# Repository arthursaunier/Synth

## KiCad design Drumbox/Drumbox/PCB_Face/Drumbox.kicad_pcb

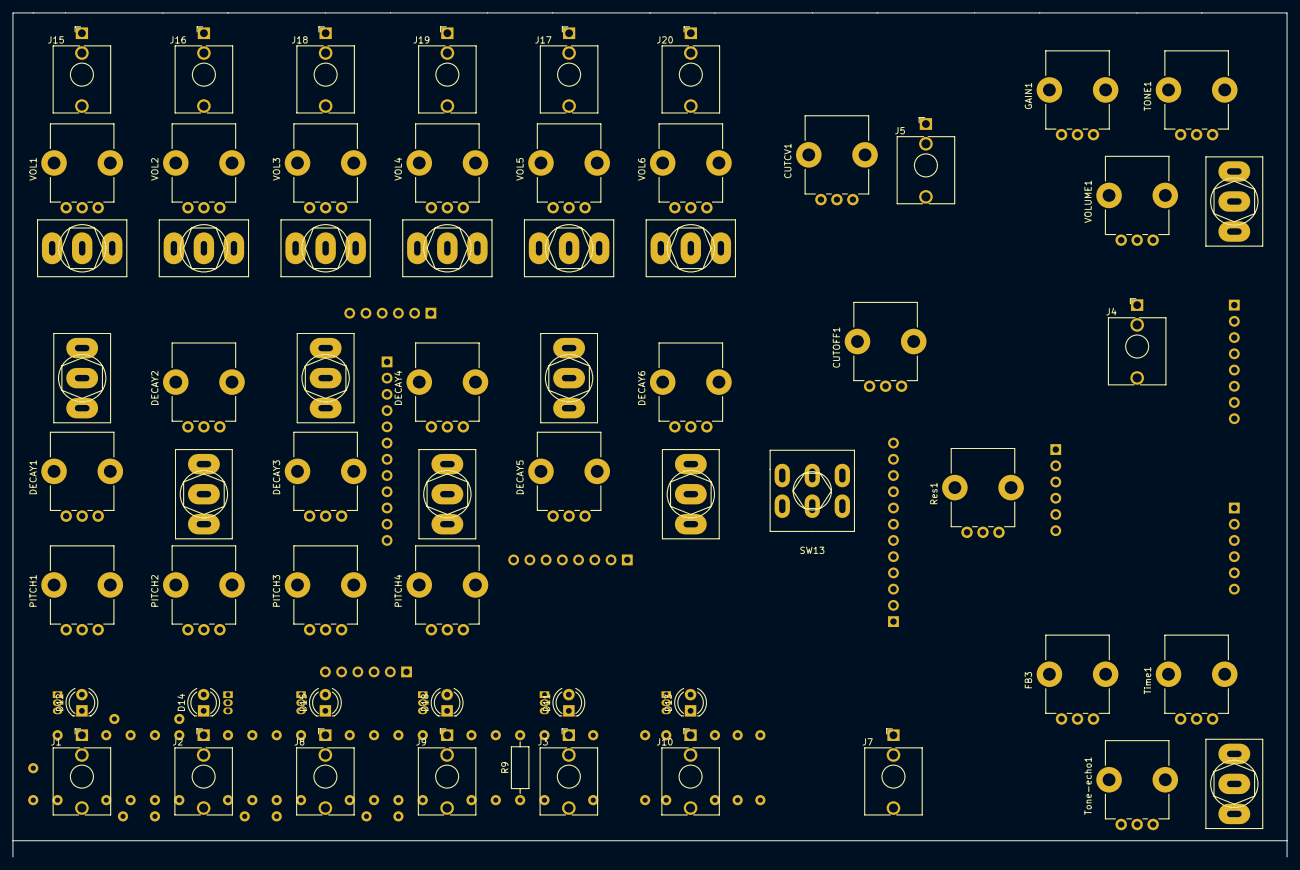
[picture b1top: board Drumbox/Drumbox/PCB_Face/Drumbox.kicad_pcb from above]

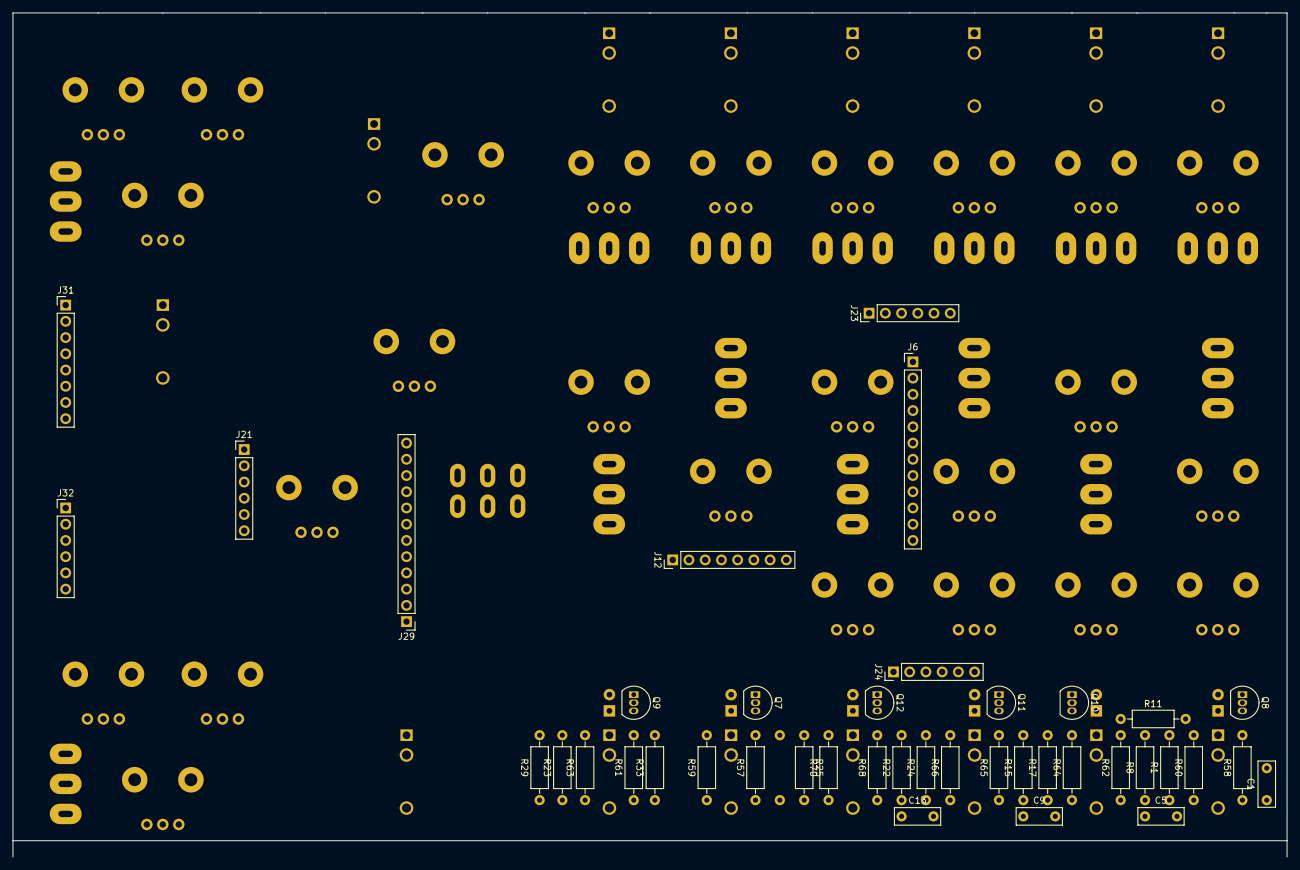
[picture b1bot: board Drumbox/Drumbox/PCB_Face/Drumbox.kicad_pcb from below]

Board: 2 copper layers, 199.4 x 132.1 mm, 103 parts (41 on the bottom side), 86 nets, no tracks yet.

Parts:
C1: 150nF; C_Disc_D7.0mm_W2.5mm_P5.00mm
C5: 33nF; C_Disc_D7.0mm_W2.5mm_P5.00mm
C9: 39nF; C_Disc_D7.0mm_W2.5mm_P5.00mm
C13: 4.7nF; C_Disc_D7.0mm_W2.5mm_P5.00mm
CUTCV1: 100k; Potentiometer_Bourns_PTV09A-1_Single_Vertical
CUTOFF1: 100k; Potentiometer_Bourns_PTV09A-1_Single_Vertical
D11: LED5; LED_D4.0mm
D12: LED1; LED_D4.0mm
D13: LED6; LED_D4.0mm
D14: LED2; LED_D4.0mm
D15: LED3; LED_D4.0mm
D18: LED4; LED_D4.0mm
DECAY1, DECAY2, DECAY3, DECAY4: 470k; Potentiometer_Bourns_PTV09A-1_Single_Vertical
DECAY5, DECAY6: 100k; Potentiometer_Bourns_PTV09A-1_Single_Vertical
FB3: 100k; Potentiometer_Bourns_PTV09A-1_Single_Vertical
GAIN1: 100k; Potentiometer_Bourns_PTV09A-1_Single_Vertical
J1: Bass IN; Jack_3.5mm_QingPu_WQP-PJ398SM_Vertical_CircularHoles
J2: HBonga IN; Jack_3.5mm_QingPu_WQP-PJ398SM_Vertical_CircularHoles
J3: Snare IN; Jack_3.5mm_QingPu_WQP-PJ398SM_Vertical_CircularHoles
J4: Aux-IN; Jack_3.5mm_QingPu_WQP-PJ398SM_Vertical_CircularHoles
J5: FilterCV; Jack_3.5mm_QingPu_WQP-PJ398SM_Vertical_CircularHoles
J6, J29: Conn_01x12_Male; PinHeader_1x12_P2.54mm_Vertical
J7: Mono-Out; Jack_3.5mm_QingPu_WQP-PJ398SM_Vertical_CircularHoles
J8: LBonga IN; Jack_3.5mm_QingPu_WQP-PJ398SM_Vertical_CircularHoles
J9: Clave IN; Jack_3.5mm_QingPu_WQP-PJ398SM_Vertical_CircularHoles
J10: HiHat IN; Jack_3.5mm_QingPu_WQP-PJ398SM_Vertical_CircularHoles
J12, J31: Conn_01x08_Male; PinHeader_1x08_P2.54mm_Vertical
J15: Bass OUT; Jack_3.5mm_QingPu_WQP-PJ398SM_Vertical_CircularHoles
J16: HBonga OUT; Jack_3.5mm_QingPu_WQP-PJ398SM_Vertical_CircularHoles
J17: Snare OUT; Jack_3.5mm_QingPu_WQP-PJ398SM_Vertical_CircularHoles
J18: LBonga OUT; Jack_3.5mm_QingPu_WQP-PJ398SM_Vertical_CircularHoles
J19: Clave OUT; Jack_3.5mm_QingPu_WQP-PJ398SM_Vertical_CircularHoles
J20: HiHat OUT; Jack_3.5mm_QingPu_WQP-PJ398SM_Vertical_CircularHoles
J21, J23, J24, J32: Conn_01x06_Male; PinHeader_1x06_P2.54mm_Vertical
PITCH1, PITCH2, PITCH3, PITCH4: 10k; Potentiometer_Bourns_PTV09A-1_Single_Vertical
Q7, Q8, Q9, Q10, Q11, Q12: 2N3904; TO-92_Inline
R1, R8, R15, R22: 12k; R_Axial_DIN0207_L6.3mm_D2.5mm_P10.16mm_Horizontal
R9, R23, R33: 4k7; R_Axial_DIN0207_L6.3mm_D2.5mm_P10.16mm_Horizontal
R11, R25, R57, R58, R61, R62, R65, R68: 47k; R_Axial_DIN0207_L6.3mm_D2.5mm_P10.16mm_Horizontal
R17, R24: 27k; R_Axial_DIN0207_L6.3mm_D2.5mm_P10.16mm_Horizontal
R29: 1M; R_Axial_DIN0207_L6.3mm_D2.5mm_P10.16mm_Horizontal
R59, R60, R63, R64, R66, R70: 2.2k; R_Axial_DIN0207_L6.3mm_D2.5mm_P10.16mm_Horizontal
Res1: 100k; Potentiometer_Bourns_PTV09A-1_Single_Vertical
SW1: Mute-1; SW_Toggle_Blue_wSlots
SW2: Mute-2; SW_Toggle_Blue_wSlots
SW3: Mute-3; SW_Toggle_Blue_wSlots
SW4: Mute-4; SW_Toggle_Blue_wSlots
SW5: Mute-5; SW_Toggle_Blue_wSlots
SW6: Mute-6; SW_Toggle_Blue_wSlots
SW7: Fx1; SW_Toggle_Blue_wSlots
SW8: Fx3; SW_Toggle_Blue_wSlots
SW9: Fx5; SW_Toggle_Blue_wSlots
SW10: Fx2; SW_Toggle_Blue_wSlots
SW11: Fx4; SW_Toggle_Blue_wSlots
SW12: Fx6; SW_Toggle_Blue_wSlots
SW13: Hpass/Lpass Switch; SW_DPDT_Toggle
SW14: Stupid ON/OFF; SW_Toggle_Blue_wSlots
SW15: Echo ON/OFF; SW_Toggle_Blue_wSlots
TONE1: 10k; Potentiometer_Bourns_PTV09A-1_Single_Vertical
Time1: 100k; Potentiometer_Bourns_PTV09A-1_Single_Vertical
Tone-echo1: 100k; Potentiometer_Bourns_PTV09A-1_Single_Vertical
VOL1, VOL2, VOL3, VOL4, VOL5, VOL6: 10k; Potentiometer_Bourns_PTV09A-1_Single_Vertical
VOLUME1: 50k; Potentiometer_Bourns_PTV09A-1_Single_Vertical

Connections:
+12V: J21.2, J29.2, R23.1, R29.1, R59.1, R60.1, R63.1, R64.1, R66.1, R70.1
AuxIn: J4.T, J21.3
CutCV: CUTCV1.2, J29.11
Cutoff: CUTOFF1.2, J29.10
DEIn1: DECAY1.1, J6.6
DEIn2: DECAY2.1, J6.5
DEIn3: DECAY3.1, J6.4
DEIn4: DECAY4.1, J6.3
DEIn5: CUTCV1.1, D11.1, D12.1, D13.1, D14.1, D15.1, D18.1, DECAY5.2, DECAY5.3, DECAY6.2, DECAY6.3, J1.S, J2.S, J3.S, J4.S, J5.S, J6.1, J6.2, J7.S, J8.S, J9.S, J10.S, J12.1, J12.2, J12.3, J15.S, J16.S, J17.S, J18.S, J19.S, J20.S, J21.1, J21.6, J29.1, J29.3, J29.4, J29.12, J32.1, PITCH2.1, PITCH3.1, PITCH4.1, R1.2, R8.2, R9.2, R11.1, R15.2, R22.2, R25.1, R33.2, Res1.1, SW13.6, Time1.3, Tone-echo1.3, VOL1.3, VOL2.3, VOL3.3, VOL4.3, VOL5.3, VOL6.3, VOLUME1.3
DEOut1: DECAY1.2, DECAY1.3, J6.12
DEOut2: DECAY2.2, DECAY2.3, J6.11
DEOut3: DECAY3.2, DECAY3.3, J6.10
DEOut4: DECAY4.2, DECAY4.3, J6.9
DEOut5: DECAY5.1, J6.8
DEOut6: DECAY6.1, J6.7
FBIn: FB3.1, J32.3
FBOut: FB3.2, J32.2
Filter: J31.6, SW7.1, SW8.1, SW9.1, SW10.1, SW11.1, SW12.1, SW13.3, SW13.4, SW15.1
FilterCV: CUTCV1.3, J5.T, J21.4
FilterOut: J7.T, J21.5
Fx: SW7.3, SW8.3, SW9.3, SW10.3, SW11.3, SW12.3, SW14.2
Fx1: SW1.1, SW7.2
Fx2: SW2.1, SW10.2
Fx3: SW3.1, SW8.2
Fx4: SW4.1, SW11.2
Fx5: SW5.1, SW9.2
Fx6: SW6.1, SW12.2
FxEcho: J31.5, SW14.1, SW15.2, VOLUME1.2
FxEchoIn: J31.7, SW15.3
FxStupidIn: J31.8, SW14.3
GainIn: GAIN1.1, J31.1
GainOut: GAIN1.2, GAIN1.3
Hpass: J29.6, SW13.5
In1: C1.1, J1.T, J24.6, R1.1, R58.1
In2: C5.1, J2.T, J24.5, R8.1, R62.1
In3: C9.1, J8.T, J24.4, R15.1, R65.1
In4: C13.1, J9.T, J24.3, R22.1, R68.1
In5: J3.T, J24.2, R9.1, R57.1
In6: J10.T, J24.1, R33.1, R61.1
LPass: J29.7, SW13.2
Mute1: J15.T, SW1.2, VOL1.2
Mute2: J16.T, SW2.2, VOL2.2
Mute3: J18.T, SW3.2, VOL3.2
Mute4: J19.T, SW4.2, VOL4.2
Mute5: J17.T, SW5.2, VOL5.2
Mute6: J20.T, SW6.2, VOL6.2
unnamed: C5.2, R11.2
unnamed: C9.2, R17.1
unnamed: C13.2, R24.1, R25.2
unnamed: D11.2, Q7.1
unnamed: D12.2, Q8.1
unnamed: D13.2, Q9.1
unnamed: D14.2, Q10.1
unnamed: D15.2, Q11.1
unnamed: D18.2, Q12.1
unnamed: Q7.2, R57.2
unnamed: Q7.3, R59.2
unnamed: Q8.2, R58.2
unnamed: Q8.3, R60.2
unnamed: Q9.2, R61.2
unnamed: Q9.3, R63.2
unnamed: Q10.2, R62.2
unnamed: Q10.3, R64.2
unnamed: Q11.2, R65.2
unnamed: Q11.3, R66.2
unnamed: Q12.2, R68.2
unnamed: Q12.3, R70.2
PIIn1: J12.4, PITCH1.1
PIOut1: J12.8, PITCH1.2, PITCH1.3
PIOut2: J12.7, PITCH2.2, PITCH2.3
PIOut3: J12.6, PITCH3.2, PITCH3.3
PIOut4: J12.5, PITCH4.2, PITCH4.3
ResIn: J29.9, Res1.3
ResOut: J29.8, Res1.2
TimeOut: J32.6, Time1.1, Time1.2
ToneEchoIn: J32.5, Tone-echo1.1
ToneEchoOut: J32.4, Tone-echo1.2
ToneIN: J31.4, TONE1.1, TONE1.2
ToneOUT: J31.3, TONE1.3
Vol1: J23.6, VOL1.1
Vol2: J23.5, VOL2.1
Vol3: J23.4, VOL3.1
Vol4: J23.3, VOL4.1
Vol5: J23.2, VOL5.1
Vol6: J23.1, VOL6.1
VolOut: J31.2, VOLUME1.1

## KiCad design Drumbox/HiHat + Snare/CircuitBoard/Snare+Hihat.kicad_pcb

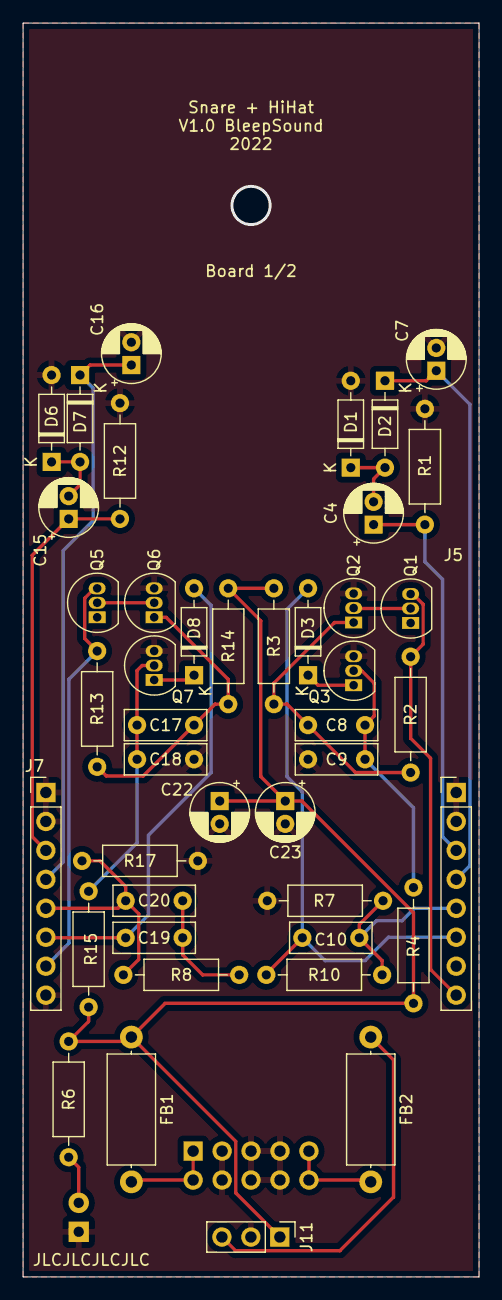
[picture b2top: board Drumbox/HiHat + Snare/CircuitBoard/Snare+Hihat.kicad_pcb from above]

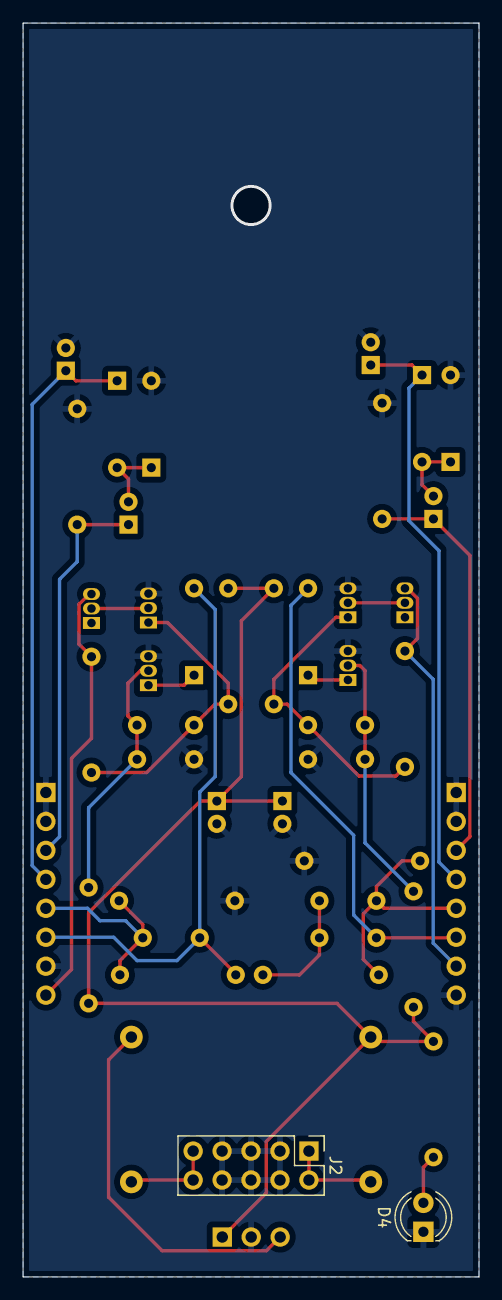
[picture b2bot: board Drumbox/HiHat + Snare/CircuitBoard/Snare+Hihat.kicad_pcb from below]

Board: 2 copper layers, 40.0 x 110.0 mm, 45 parts (2 on the bottom side), 27 nets.

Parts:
C4, C7, C15, C16: 10µF; CP_Radial_D5.0mm_P2.00mm
C8, C17: 1µF; C_Disc_D7.0mm_W2.5mm_P5.00mm
C9: 0.1µF; C_Disc_D7.0mm_W2.5mm_P5.00mm
C10, C20: .1µF; C_Disc_D7.0mm_W2.5mm_P5.00mm
C18: 10nF; C_Disc_D7.0mm_W2.5mm_P5.00mm
C19: 680pF; C_Disc_D7.0mm_W2.5mm_P5.00mm
C22, C23: 100µ; CP_Radial_D5.0mm_P2.00mm
D1, D2, D3, D6, D7, D8: 1N4148; D_DO-35_SOD27_P7.62mm_Horizontal
D4: LED-12V; LED_D4.0mm
FB1, FB2: 10R; L_Axial_L9.5mm_D4.0mm_P12.70mm_Horizontal_Fastron_SMCC
J2: Power Input; PinHeader_2x05_P2.54mm_Vertical
J5, J7: Conn_01x08_Male; PinHeader_1x08_P2.54mm_Vertical
J11: Conn_01x03_Male; PinHeader_1x03_P2.54mm_Vertical
Q1, Q2, Q3, Q5, Q6, Q7: BC546; TO-92_Inline
R1, R3, R12, R14: 4k7; R_Axial_DIN0207_L6.3mm_D2.5mm_P10.16mm_Horizontal
R2, R13: 47k; R_Axial_DIN0207_L6.3mm_D2.5mm_P10.16mm_Horizontal
R4, R7, R15, R17: 1M; R_Axial_DIN0207_L6.3mm_D2.5mm_P10.16mm_Horizontal
R6: 2.2k; R_Axial_DIN0207_L6.3mm_D2.5mm_P10.16mm_Horizontal
R8, R10: 0R; R_Axial_DIN0207_L6.3mm_D2.5mm_P10.16mm_Horizontal

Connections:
+12V: C22.1, C23.1, FB1.1, J11.1, R3.1, R4.1, R6.1, R14.1, R15.1
-12V: FB2.1, J11.3
/DeH: J5.8, Q1.3 (E), R2.1
/HiDH: J7.7, Q5.3 (E), R13.1
/HiH: C16.1, D7.1 (K), J7.4
/HiI: C15.1, J7.3, R12.1
/HiO: C20.2, J7.5, R8.1, R17.1
/Ho: C19.1, D8.2 (A), J7.6
/SnH: C7.1, D2.1 (K), J5.4
/SnI: C4.1, J5.3, R1.1
/SnO: C10.2, J5.5, R7.1, R10.1
/So: C10.1, D3.2 (A), J5.6, R10.2
GND: C7.2, C9.1, C16.2, C18.1, C22.2, C23.2, D1.2 (A), D4.1 (K), D6.2 (A), J2.3, J2.4, J2.5, J2.6, J2.7, J2.8, J5.1, J5.2, J5.7, J7.1, J7.2, J7.8, J11.2, Q2.3 (E), Q3.3 (E), Q6.3 (E), Q7.3 (E), R1.2, R7.2, R12.2, R17.2
unnamed: C4.2, D1.1 (K), D2.2 (A)
unnamed: C8.1, Q2.1 (C), R2.2, R3.2
unnamed: C8.2, C9.2, Q3.2 (B), R4.2
unnamed: C15.2, D6.1 (K), D7.2 (A)
unnamed: C17.1, Q6.1 (C), R13.2, R14.2
unnamed: C17.2, C18.2, Q7.2 (B), R15.2
unnamed: C19.2, C20.1, R8.2
unnamed: D3.1 (K), Q3.1 (C)
unnamed: D4.2 (A), R6.2
unnamed: D8.1 (K), Q7.1 (C)
unnamed: FB1.2, J2.1, J2.2
unnamed: FB2.2, J2.9, J2.10
unnamed: Q1.2 (B), Q2.2 (B)
unnamed: Q5.2 (B), Q6.2 (B)

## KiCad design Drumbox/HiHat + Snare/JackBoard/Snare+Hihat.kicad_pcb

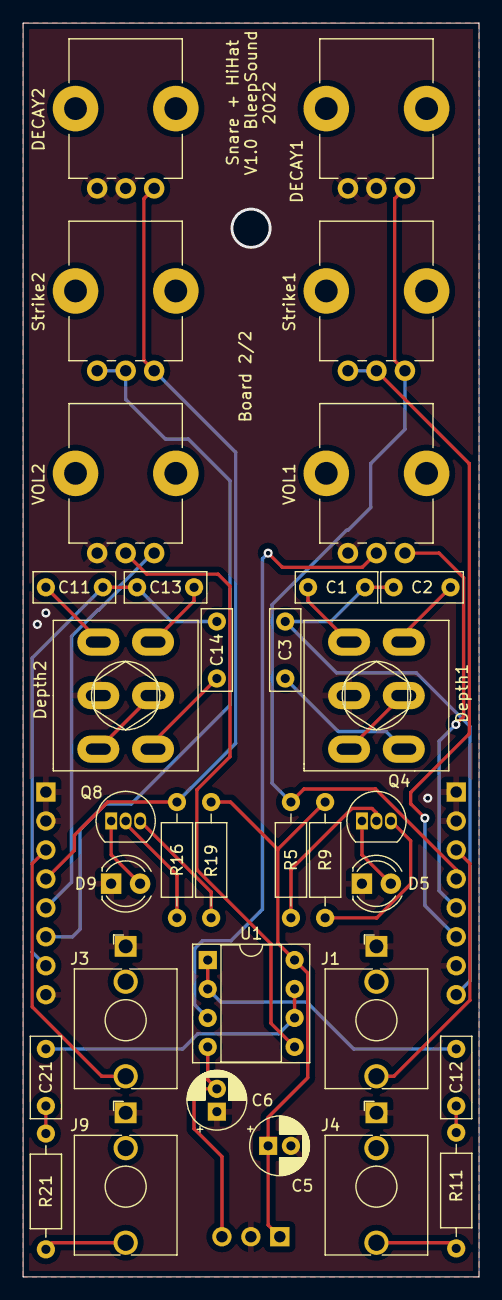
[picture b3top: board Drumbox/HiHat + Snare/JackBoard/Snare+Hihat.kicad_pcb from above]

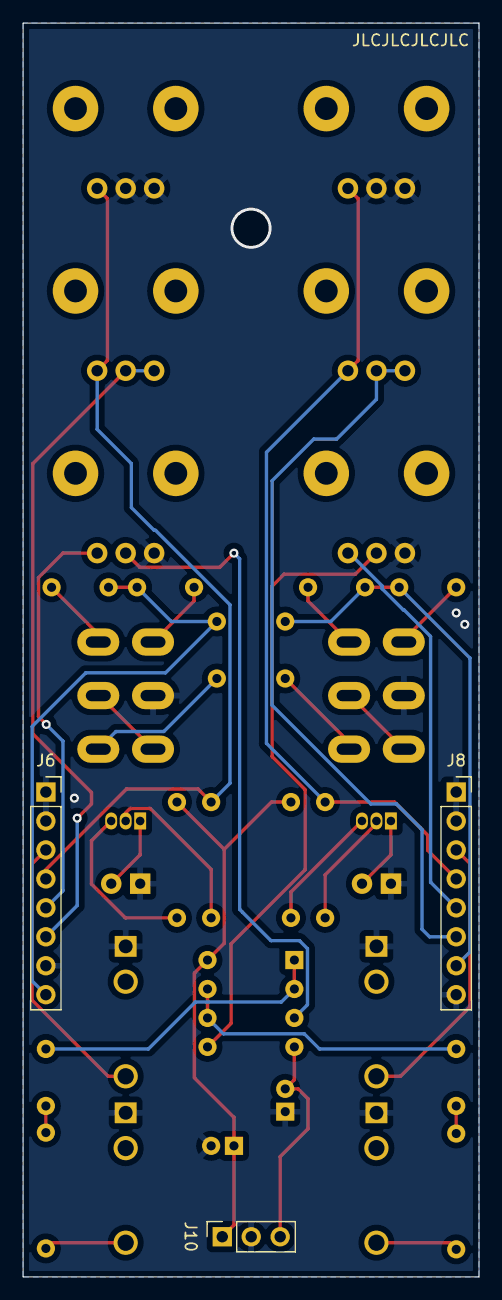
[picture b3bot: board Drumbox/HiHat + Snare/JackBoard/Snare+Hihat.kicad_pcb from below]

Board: 2 copper layers, 40.0 x 110.0 mm, 36 parts (3 on the bottom side), 35 nets.

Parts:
C1, C11, C12, C21: 10µF; C_Disc_D7.0mm_W2.5mm_P5.00mm
C2, C13: 1µF; C_Disc_D7.0mm_W2.5mm_P5.00mm
C3, C14: 0.1µF; C_Disc_D7.0mm_W2.5mm_P5.00mm
C5, C6: 10µ; CP_Radial_D5.0mm_P2.00mm
D5: Trig Snare; LED_D4.0mm
D9: Trig_HiHat; LED_D4.0mm
DECAY1, DECAY2: 100k; Potentiometer_Bourns_PTV09A-1_Single_Vertical
Depth1, Depth2: SW_Push_DPDT; SW_DPDT_Toggle
J1: Snare IN; Jack_3.5mm_QingPu_WQP-PJ398SM_Vertical_CircularHoles
J3: HiHat IN; Jack_3.5mm_QingPu_WQP-PJ398SM_Vertical_CircularHoles
J4: Snare OUT; Jack_3.5mm_QingPu_WQP-PJ398SM_Vertical_CircularHoles
J6, J8: Conn_01x08_Female; PinSocket_1x08_P2.54mm_Vertical
J9: HiHat OUT; Jack_3.5mm_QingPu_WQP-PJ398SM_Vertical_CircularHoles
J10: Conn_01x03_Female; PinSocket_1x03_P2.54mm_Vertical
Q4, Q8: 2N3904; TO-92_Inline
R5, R16: 100k; R_Axial_DIN0207_L6.3mm_D2.5mm_P10.16mm_Horizontal
R9, R11, R19, R21: 1k; R_Axial_DIN0207_L6.3mm_D2.5mm_P10.16mm_Horizontal
Strike1, Strike2: 100k; Potentiometer_Bourns_PTV09A-1_Single_Vertical
U1: TL072; DIP-8_W7.62mm_Socket
VOL1, VOL2: 10k; Potentiometer_Bourns_PTV09A-1_Single_Vertical

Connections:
+12V: C5.1, J10.1, R9.1, R19.1, U1.8 (V+)
-12V: C6.2, J10.3, U1.4 (V-)
/DeH: C1.1, C2.1, C3.1, J6.8
/HiDH: C11.1, C13.1, C14.1, J8.7
/HiH: DECAY2.1, J8.4, R16.1, Strike2.1
/HiI: J3.T, J8.3
/HiO: J8.5, VOL2.1
/Ho: J8.6, Strike2.2, Strike2.3
/SnH: DECAY1.1, J6.4, R5.1, Strike1.1
/SnI: J1.T, J6.3
/SnO: J6.5, VOL1.1
/So: J6.6, Strike1.2, Strike1.3
GND: C5.2, C6.1, D5.1 (K), D9.1 (K), DECAY1.2, DECAY1.3, DECAY2.2, DECAY2.3, Depth1.2 (B), Depth2.2 (B), J1.S, J3.S, J4.S, J6.1, J6.2, J6.7, J8.1, J8.2, J8.8, J9.S, J10.2, VOL1.3, VOL2.3
unnamed: C1.2, Depth1.1 (A)
unnamed: C2.2, Depth1.4 (A)
unnamed: C3.2, Depth1.6 (C)
unnamed: C11.2, Depth2.1 (A)
unnamed: C12.2, R11.2
unnamed: C13.2, Depth2.4 (A)
unnamed: C14.2, Depth2.6 (C)
unnamed: C21.1, U1.6 (-), U1.7
unnamed: C21.2, R21.2
unnamed: D5.2 (A), Q4.1 (E)
unnamed: D9.2 (A), Q8.1 (E)
unnamed: Depth1.3 (C), Depth1.5 (B)
unnamed: Depth2.3 (C), Depth2.5 (B)
unnamed: Q4.2 (B), R5.2
unnamed: Q4.3 (C), R9.2
unnamed: Q8.2 (B), R16.2
unnamed: Q8.3 (C), R19.2
unnamed: J4.T, R11.1
unnamed: J9.T, R21.1
unnamed: C12.1, U1.1, U1.2 (-)
unnamed: U1.3 (+), VOL1.2
unnamed: U1.5 (+), VOL2.2

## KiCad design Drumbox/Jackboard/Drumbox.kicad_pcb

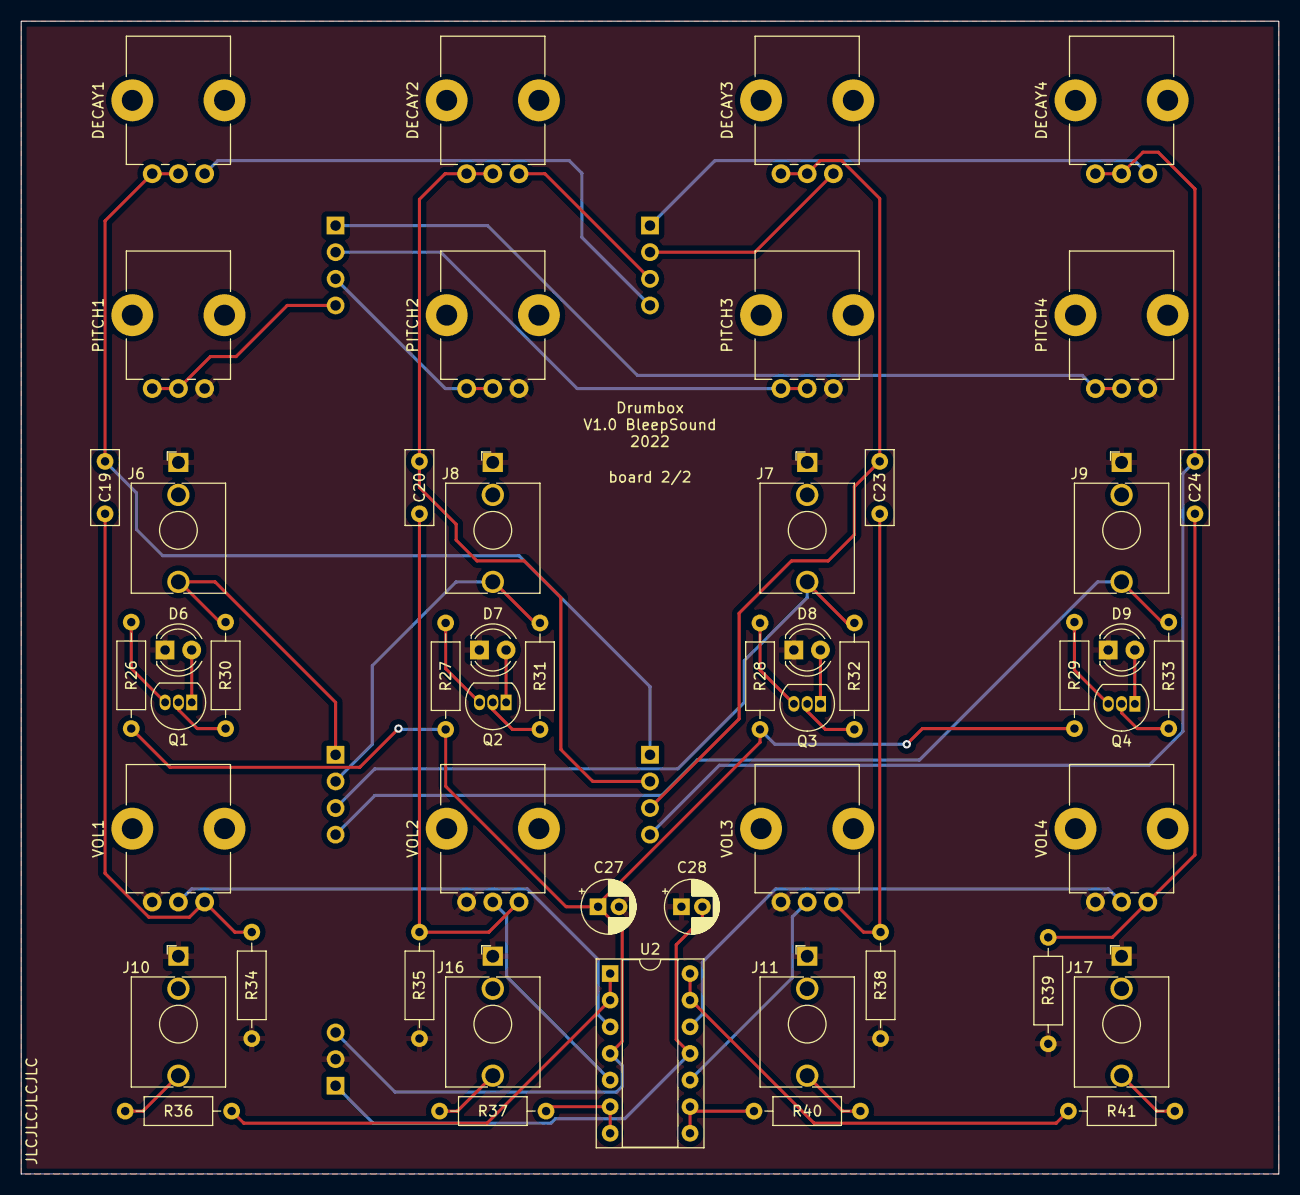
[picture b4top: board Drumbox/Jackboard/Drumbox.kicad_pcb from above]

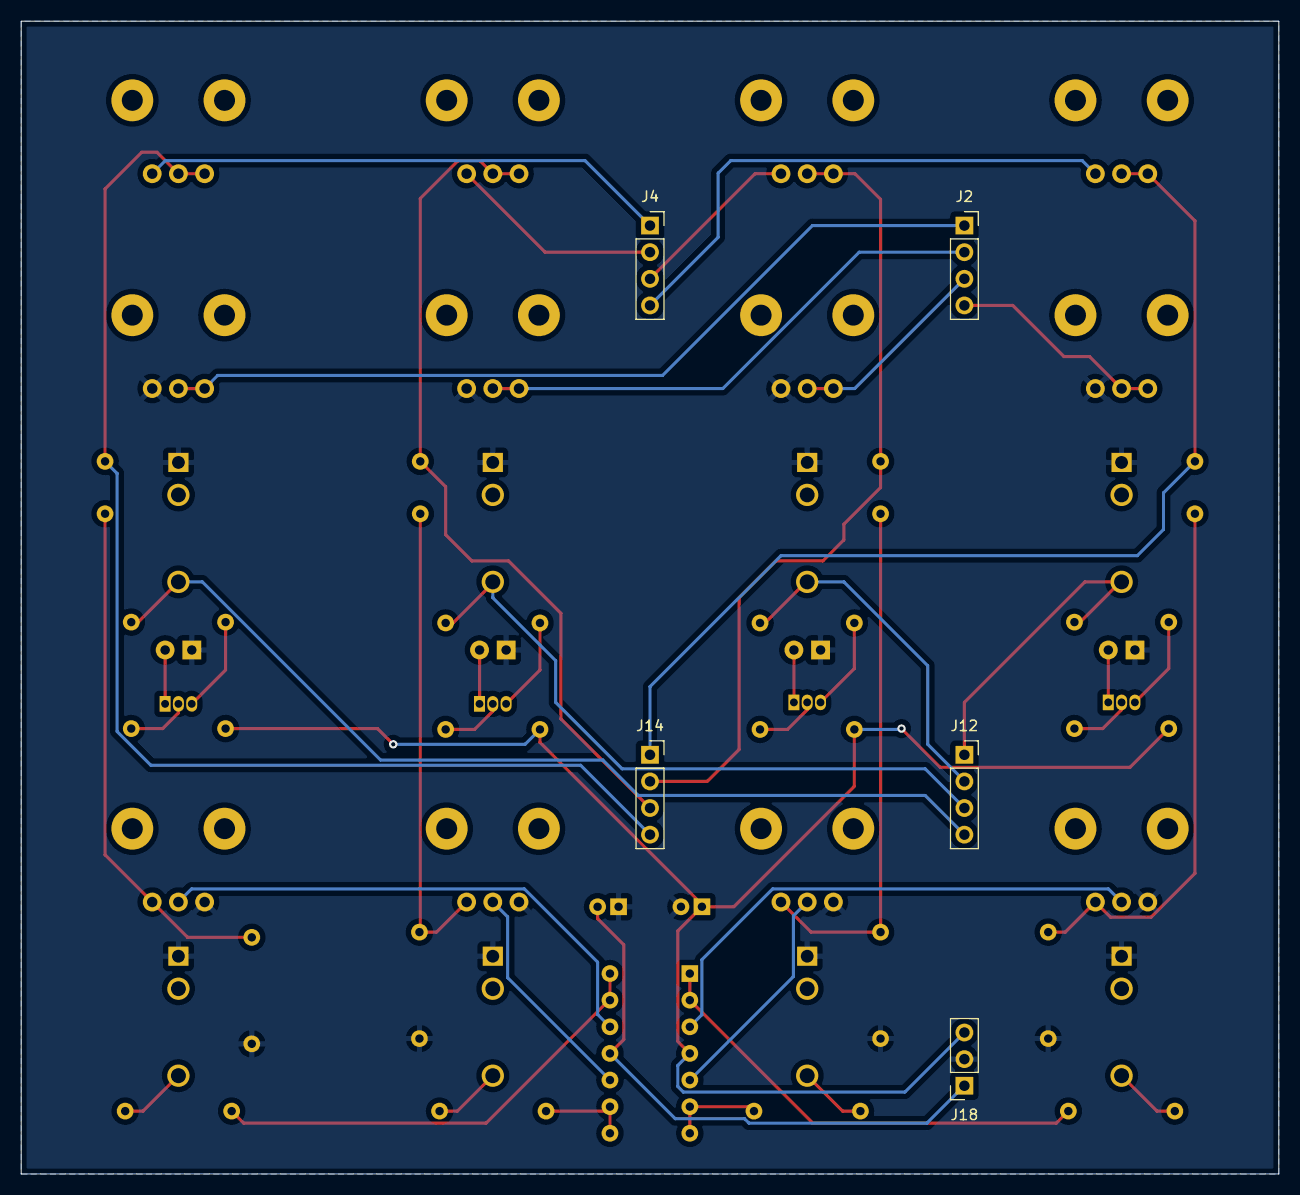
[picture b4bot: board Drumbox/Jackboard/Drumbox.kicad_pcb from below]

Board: 2 copper layers, 120.0 x 110.0 mm, 56 parts (5 on the bottom side), 47 nets.

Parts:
C19, C20, C23, C24: .1µF; C_Disc_D7.0mm_W2.5mm_P5.00mm
C27, C28: 100n; CP_Radial_D5.0mm_P2.00mm
D6: LED1; LED_D4.0mm
D7: LED2; LED_D4.0mm
D8: LED3; LED_D4.0mm
D9: LED4; LED_D4.0mm
DECAY1, DECAY2, DECAY3, DECAY4: 470k; Potentiometer_Bourns_PTV09A-1_Single_Vertical
J2, J4, J12, J14: Conn_01x04_Female; PinSocket_1x04_P2.54mm_Vertical
J6: Bass IN; Jack_3.5mm_QingPu_WQP-PJ398SM_Vertical_CircularHoles
J7: LBonga IN; Jack_3.5mm_QingPu_WQP-PJ398SM_Vertical_CircularHoles
J8: HBonga IN; Jack_3.5mm_QingPu_WQP-PJ398SM_Vertical_CircularHoles
J9: Clave IN; Jack_3.5mm_QingPu_WQP-PJ398SM_Vertical_CircularHoles
J10: Bass OUT; Jack_3.5mm_QingPu_WQP-PJ398SM_Vertical_CircularHoles
J11: LBonga OUT; Jack_3.5mm_QingPu_WQP-PJ398SM_Vertical_CircularHoles
J16: HBonga OUT; Jack_3.5mm_QingPu_WQP-PJ398SM_Vertical_CircularHoles
J17: Clave OUT; Jack_3.5mm_QingPu_WQP-PJ398SM_Vertical_CircularHoles
J18: Conn_01x03_Female; PinSocket_1x03_P2.54mm_Vertical
PITCH1, PITCH2, PITCH3, PITCH4: 10k; Potentiometer_Bourns_PTV09A-1_Single_Vertical
Q1, Q2, Q3, Q4: 2N3904; TO-92_Inline
R26, R27, R28, R29, R36, R37, R40, R41: 1k; R_Axial_DIN0207_L6.3mm_D2.5mm_P10.16mm_Horizontal
R30, R31, R32, R33: 47k; R_Axial_DIN0207_L6.3mm_D2.5mm_P10.16mm_Horizontal
R34, R35, R38, R39: 1M; R_Axial_DIN0207_L6.3mm_D2.5mm_P10.16mm_Horizontal
U2: TL074; DIP-14_W7.62mm_Socket
VOL1, VOL2, VOL3, VOL4: 10k; Potentiometer_Bourns_PTV09A-1_Single_Vertical

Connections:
+12V: C27.1, J18.3, R26.1, R27.1, R28.1, R29.1, U2.4 (V+)
-12V: C28.2, J18.1, U2.11 (V-)
DEIn1: DECAY1.1, J4.4
DEIn2: DECAY2.1, J4.3
DEIn3: DECAY3.1, J4.2
DEIn4: DECAY4.1, J4.1
GND: C27.2, C28.1, D6.1 (K), D7.1 (K), D8.1 (K), D9.1 (K), J6.S, J7.S, J8.S, J9.S, J10.S, J11.S, J16.S, J17.S, J18.2, PITCH1.1, PITCH2.1, PITCH3.1, PITCH4.1, R34.2, R35.2, R38.2, R39.2, VOL1.3, VOL2.3, VOL3.3, VOL4.3
In1: J6.T, J12.1, R30.1
In2: J8.T, J12.2, R31.1
In3: J7.T, J12.3, R32.1
In4: J9.T, J12.4, R33.1
unnamed: C19.2, R34.1, VOL1.1
unnamed: C20.2, R35.1, VOL2.1
unnamed: C23.2, R38.1, VOL3.1
unnamed: C24.2, R39.1, VOL4.1
unnamed: D6.2 (A), Q1.1 (E)
unnamed: D7.2 (A), Q2.1 (E)
unnamed: D8.2 (A), Q3.1 (E)
unnamed: D9.2 (A), Q4.1 (E)
unnamed: Q1.2 (B), R30.2
unnamed: Q1.3 (C), R26.2
unnamed: Q2.2 (B), R31.2
unnamed: Q2.3 (C), R27.2
unnamed: Q3.2 (B), R32.2
unnamed: Q3.3 (C), R28.2
unnamed: Q4.2 (B), R33.2
unnamed: Q4.3 (C), R29.2
unnamed: R36.2, U2.1, U2.2 (-)
unnamed: R37.2, U2.6 (-), U2.7
unnamed: R40.2, U2.8, U2.9 (-)
unnamed: R41.2, U2.13 (-), U2.14
unnamed: U2.3 (+), VOL1.2
unnamed: U2.5 (+), VOL2.2
unnamed: U2.10 (+), VOL3.2
unnamed: U2.12 (+), VOL4.2
O1: C19.1, DECAY1.2, DECAY1.3, J14.1
O2: C20.1, DECAY2.2, DECAY2.3, J14.2
O3: C23.1, DECAY3.2, DECAY3.3, J14.3
O4: C24.1, DECAY4.2, DECAY4.3, J14.4
Out1: J10.T, R36.1
Out2: J16.T, R37.1
Out3: J11.T, R40.1
Out4: J17.T, R41.1
PIOut1: J2.4, PITCH1.2, PITCH1.3
PIOut2: J2.3, PITCH2.2, PITCH2.3
PIOut3: J2.2, PITCH3.2, PITCH3.3
PIOut4: J2.1, PITCH4.2, PITCH4.3

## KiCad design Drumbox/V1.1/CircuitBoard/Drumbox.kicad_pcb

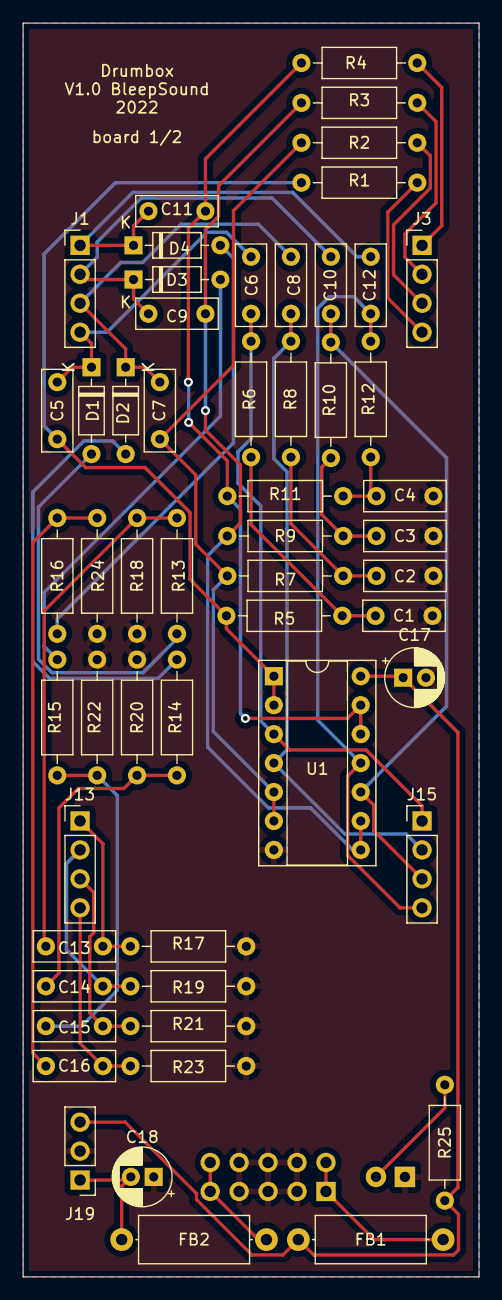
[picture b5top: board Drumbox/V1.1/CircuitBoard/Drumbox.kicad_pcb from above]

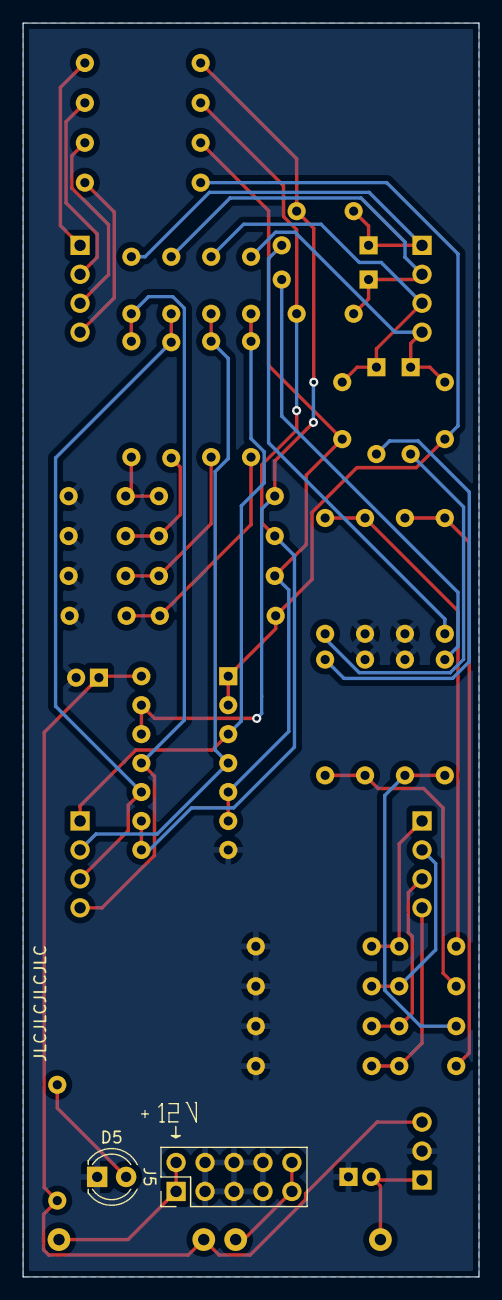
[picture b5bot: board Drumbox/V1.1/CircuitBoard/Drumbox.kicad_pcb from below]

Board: 2 copper layers, 40.0 x 110.0 mm, 57 parts (2 on the bottom side), 38 nets.

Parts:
C1, C13: 150nF; C_Disc_D7.0mm_W2.5mm_P5.00mm
C2, C14: 33nF; C_Disc_D7.0mm_W2.5mm_P5.00mm
C3, C15: 39nF; C_Disc_D7.0mm_W2.5mm_P5.00mm
C4: 56nF; C_Disc_D7.0mm_W2.5mm_P5.00mm
C5, C6: 47nF; C_Disc_D7.0mm_W2.5mm_P5.00mm
C7, C8: 10nF; C_Disc_D7.0mm_W2.5mm_P5.00mm
C9, C10: 12nF; C_Disc_D7.0mm_W2.5mm_P5.00mm
C11, C12: 1.5nF; C_Disc_D7.0mm_W2.5mm_P5.00mm
C16: 4.7nF; C_Disc_D7.0mm_W2.5mm_P5.00mm
C17, C18: 10µ; CP_Radial_D5.0mm_P2.00mm
D1, D2, D3, D4: 1N4148; D_DO-35_SOD27_P7.62mm_Horizontal
D5: LED-12V; LED_D4.0mm
FB1, FB2: 10R; L_Axial_L9.5mm_D4.0mm_P12.70mm_Horizontal_Fastron_SMCC
J1, J3, J13, J15: Conn_01x04_Male; PinHeader_1x04_P2.54mm_Vertical
J5: Power Input; PinHeader_2x05_P2.54mm_Vertical
J19: Conn_01x03_Male; PinHeader_1x03_P2.54mm_Vertical
R1, R2, R3, R4: 150k; R_Axial_DIN0207_L6.3mm_D2.5mm_P10.16mm_Horizontal
R5, R6, R7, R8, R9, R10, R11, R12: 68k; R_Axial_DIN0207_L6.3mm_D2.5mm_P10.16mm_Horizontal
R13, R14, R15, R16: 27k; R_Axial_DIN0207_L6.3mm_D2.5mm_P10.16mm_Horizontal
R17, R19, R21, R23: 12k; R_Axial_DIN0207_L6.3mm_D2.5mm_P10.16mm_Horizontal
R18, R20, R22, R24: 47k; R_Axial_DIN0207_L6.3mm_D2.5mm_P10.16mm_Horizontal
R25: 2.2k; R_Axial_DIN0207_L6.3mm_D2.5mm_P10.16mm_Horizontal
U1: 4011; DIP-14_W7.62mm_Socket

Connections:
+12V: C17.1, FB1.1, J19.3, R25.1, U1.14 (VDD)
-12V: C18.2, FB2.1, J19.1
DEIn1: J3.4, R1.1
DEIn2: J3.3, R2.1
DEIn3: J3.2, R3.1
DEIn4: J3.1, R4.1
GND: C1.2, C2.2, C3.2, C4.2, C17.2, C18.1, D5.1 (K), J5.3, J5.4, J5.5, J5.6, J5.7, J5.8, J19.2, R17.2, R18.1, R19.2, R20.1, R21.2, R22.1, R23.2, R24.1, U1.7 (VSS)
In1: C13.1, J13.1, R17.1
In2: C14.1, J13.2, R19.1
In3: C15.1, J13.3, R21.1
In4: C16.1, J13.4, R23.1
unnamed: C1.1, R5.1, R6.2
unnamed: C2.1, R7.1, R8.2
unnamed: C3.1, R9.1, R10.2
unnamed: C4.1, R11.1, R12.2
unnamed: C5.1, R1.2, R5.2, U1.1, U1.2
unnamed: C7.1, R2.2, R7.2, U1.5, U1.6
unnamed: C9.1, R3.2, R9.2, U1.8, U1.9
unnamed: C11.1, R4.2, R11.2, U1.12, U1.13
unnamed: C13.2, R13.1, R18.2
unnamed: C14.2, R14.1, R20.2
unnamed: C15.2, R15.1, R22.2
unnamed: C16.2, R16.1, R24.2
unnamed: D1.2 (A), R13.2
unnamed: D2.2 (A), R14.2
unnamed: D3.2 (A), R15.2
unnamed: D4.2 (A), R16.2
unnamed: D5.2 (A), R25.2
unnamed: FB1.2, J5.1, J5.2
unnamed: FB2.2, J5.9, J5.10
O1: C6.2, J15.1, R6.1, U1.3
O2: C8.2, J15.2, R8.1, U1.4
O3: C10.2, J15.3, R10.1, U1.10
O4: C12.2, J15.4, R12.1, U1.11
PIOut1: C5.2, C6.1, D1.1 (K), J1.4
PIOut2: C7.2, C8.1, D2.1 (K), J1.3
PIOut3: C9.2, C10.1, D3.1 (K), J1.2
PIOut4: C11.2, C12.1, D4.1 (K), J1.1
